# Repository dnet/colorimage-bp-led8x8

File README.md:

Color Image Budapest 8 by 8 LED display driver
==============================================

Building and burning the firmware
---------------------------------

Dependencies: `make` `gcc-avr` `avrdude`

	make program

If you haven't changed the clock settings to 8 MHz and no clock divider,
you'll also need to run `make burn-fuse`

Protocol
--------

One-way communication is done in 1 byte serial (USART) packets @ 9600 bps:

	(MSB) RRRS PPPP (LSB)

 - 3 bits for row selection (0-7, 0 is the topmost)
 - 1 bit for side selection (0 is left, 1 is right)
 - 4 bits pixel payload (LSB is the rightmost)

### Examples ###

(dots represent unchanged pixels)

Packet: `01001011` (0x4b)

Display:

	. . . . . . . .
	. . . . . . . .
	. . . . . . . .
	. . . . . . . .
	x   x x . . . .
	. . . . . . . .
	. . . . . . . .
	. . . . . . . .

Packet: `11111111` (0xff)

Display:

	. . . . . . . .
	. . . . . . . .
	. . . . . . . .
	. . . . . . . .
	. . . . . . . .
	. . . . . . . .
	. . . . . . . .
	. . . . x x x x

Controller board
----------------

 - ATtiny2313 microcontroller running at 8 MHz (internal clock)
   - PORT B (PB0-PB1) for column addressing with a shift register
   - PORT D (PD2-PD5) for row addressing
 - 74HC138 3 to 8-line demux (row selection)
 - 74HC164 8 bit serial-in parallel-out shift register (column buffer)
 - transistors for driving

### Schematics ###

Display board layout
--------------------

 - 5 LEDs are in series for each pixel
 - rows are numbered from top to bottom
 - cols are numbered from right to left
 - `right` and `left` are referred to as when looking at the LEDs
 - row pins must be positive, col pins must be grounded for LEDs to light

ASCII art layout:

	.------------------------------.
	|        COLOR  IMAGE    (TOP) |
	|          BUDAPEST            |
	|                              |
	|          ++++++++ (row pins) |
	|                              |
	|                              |
	|                              |
	|                              |
	|          ........ (blank)    |
	|                              |
	|                              |
	|          ++++++++ (col pins) |
	|                              |
	| (RIGHT)   (back)      (LEFT) |
	'------------------------------'

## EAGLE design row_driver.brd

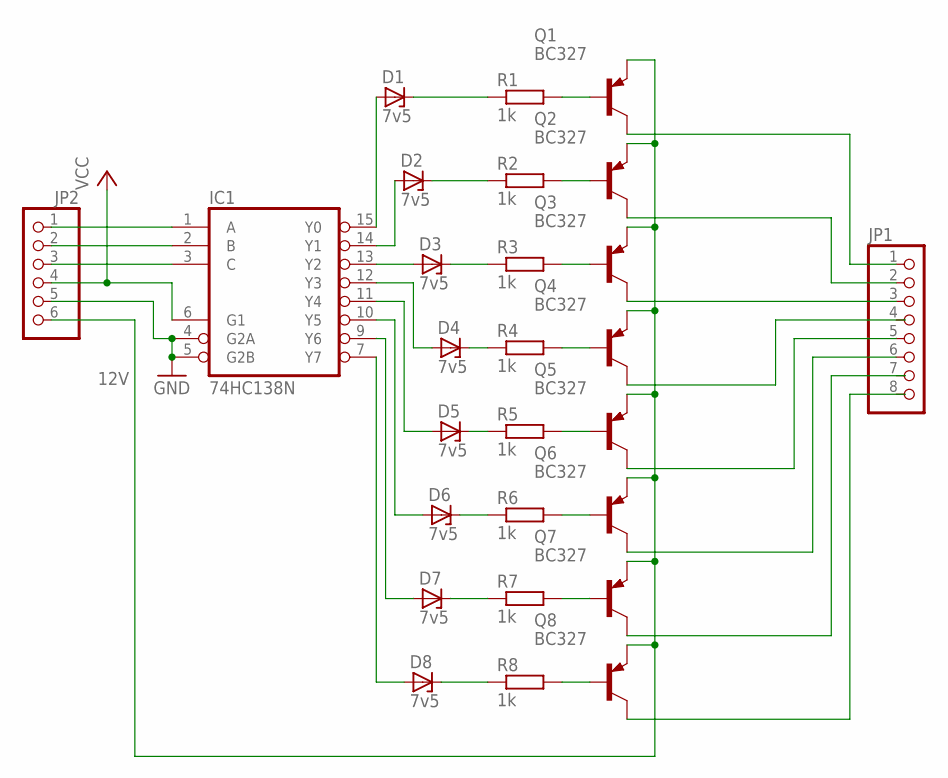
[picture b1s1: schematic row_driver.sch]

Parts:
D1, D2, D3, D4, D5, D6, D7, D8: 7v5; DO34Z7
IC1: 74HC138N; DIL16
JP1: PINHD-1X8; 1X08
JP2: PINHD-1X6; 1X06
Q1, Q2, Q3, Q4, Q5, Q6, Q7, Q8: BC327; TO92
R1, R2, R3, R4, R5, R6, R7, R8: 1k; 0207/12

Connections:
12V: JP2.6, Q1.1 (E), Q2.1 (E), Q3.1 (E), Q4.1 (E), Q5.1 (E), Q6.1 (E), Q7.1 (E), Q8.1 (E)
GND: IC1.4 (G2A), IC1.5 (G2B), IC1.8 (GND), JP2.5
unnamed: D1.A, IC1.15 (Y0)
unnamed: D5.A, IC1.11 (Y4)
unnamed: IC1.1 (A), JP2.1
unnamed: IC1.2 (B), JP2.2
unnamed: IC1.3 (C), JP2.3
unnamed: D4.C, R4.1
unnamed: Q4.2 (B), R4.2
unnamed: Q5.2 (B), R5.2
unnamed: D6.C, R6.1
unnamed: Q6.2 (B), R6.2
unnamed: Q7.2 (B), R7.2
unnamed: D7.C, R7.1
unnamed: D8.C, R8.1
unnamed: D1.C, R1.1
unnamed: D2.C, R2.1
unnamed: D3.C, R3.1
unnamed: Q3.2 (B), R3.2
unnamed: Q2.2 (B), R2.2
unnamed: Q1.2 (B), R1.2
unnamed: JP1.1, Q1.3 (C)
unnamed: JP1.2, Q2.3 (C)
unnamed: JP1.3, Q3.3 (C)
unnamed: JP1.5, Q5.3 (C)
unnamed: JP1.6, Q6.3 (C)
unnamed: D2.A, IC1.14 (Y1)
unnamed: D3.A, IC1.13 (Y2)
unnamed: D4.A, IC1.12 (Y3)
unnamed: D8.A, IC1.7 (Y7)
unnamed: D7.A, IC1.9 (Y6)
unnamed: D6.A, IC1.10 (Y5)
VCC: IC1.6 (G1), IC1.16 (VCC), JP2.4

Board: 2 copper layers, 27 parts (0 on the bottom side), 33 nets, no tracks yet.

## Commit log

2015-01-08 README: added newline to fix GitHub Markdown rendering
2015-01-08 README: added paragraph to fix GitHub Markdown rendering
2015-01-08 added Python client
2015-01-22 added row driver schematic
2015-01-22 row_driver: fixed R8-Q8 wire
2015-01-30 Makefile: fixed hex file name in target 'program'
2015-01-30 fixed ROW_MASK (external demux)
2015-01-30 load checkboard pattern at init
2015-01-30 replaced direct drive with bit-bang SPI
2015-01-30 use symbolic constant instead of magic numbers
2015-01-30 unroll loops
2015-02-01 use symbolic constants for DDRs
2015-02-03 redefine ROW_MASK using NUM_ROWS
2015-02-03 use semantic alias for row port and merge update
2015-02-03 fixed prefix increment
2015-02-07 enabled extra warnings
2015-02-07 set frequency to 8 MHz
2015-02-07 moved pixel shift code to main loop
2015-02-07 set default layout to pixel ID
2015-02-07 updated README to reflect 8 MHz clock
2015-02-07 updated README to reflect prototype hardware
2015-02-09 added column driver schematics
2015-02-09 row_driver: yet another wire gap
2015-02-09 row_driver: added GND and VCC
